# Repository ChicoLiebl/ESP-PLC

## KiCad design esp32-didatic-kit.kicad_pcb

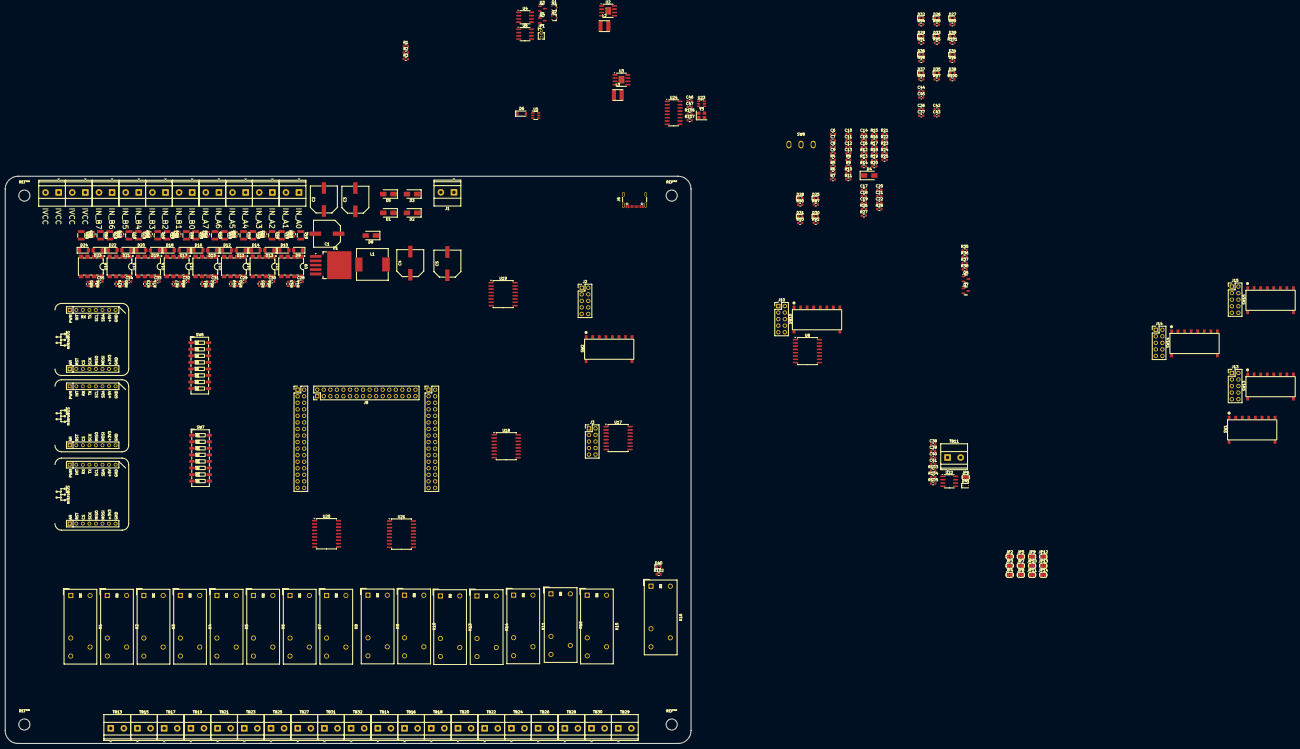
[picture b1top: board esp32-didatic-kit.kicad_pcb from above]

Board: 2 copper layers, 266.0 x 220.0 mm, 298 parts (0 on the bottom side), 241 nets, no tracks yet.

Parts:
C1, C2, C3, C4, C5: 330uF; CAP-SMD_BD10.0-L10.3-W10.3-LS10.9-FD
C6, C10, C20: 1uF; C_0603_1608Metric
C7, C8, C9, C11, C12, C13: 22uF; C_0603_1608Metric
C14, C21: 100pF; C_0603_1608Metric
C15, C16, C17, C18, C19, C28, C29, C30, C31, C32, C33, C34, C35, C36, C37, C42, C43, C44, C45: 0.1uF; C_0603_1608Metric
C22: 2.2uF; C_0603_1608Metric
C38, C40, C41: 30pF 50v; C_0603_1608Metric
C39: 100nF; C_0603_1608Metric
C46, C47: 22pF; C_0603_1608Metric
CON1, CON2, CON3: MIKROBUS_HOST_CONN
D1, D2, D3, D4, D5, D8: SS24; D_SMA
D6: PMEG3010ER,115; D_SOD-123
D9, D10, D11, D12, D13, D14, D15, D16, D17, D18, D19, D20, D21, D22, D23, D24: LL4148; D_MiniMELF
D25, D26, D27, D28, D29, D30, D31, D32, D33, D34, D35, D36, D37, D38, D39, D40: LED; LED_0603_1608Metric
D41: BAT54J; D_SOD-323F
J1: Power Input; TerminalBlock_Phoenix_MKDS-1,5-2-5.08_1x02_P5.08mm_Horizont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
J2, J3, J10, J13, J14, J15: Conn_02x05_Odd_Even; PinHeader_2x05_P2.54mm_Vertical
J6: USB_C_Receptacle; USB_C_Receptacle_GCT_USB4105-xx-A_16P_TopMnt_Horizontal
J8: MCU_MODULE_CONN; mcu_conn
JP1: REF-SEL; PinHeader_1x03_P1.27mm_Vertical
JP2, JP3, JP4, JP5, JP7, JP8, JP9, JP10, JP11, JP12, JP13, JP14: Jumper_2_Bridged; SolderJumper-2_P1.3mm_Bridged_RoundedPad1.0x1.5mm
JP6: SolderJumper_2_Open; SolderJumper-2_P1.3mm_Open_RoundedPad1.0x1.5mm
K1, K2, K3, K4, K5, K6, K7, K8, K9, K10, K11, K12, K13, K14, K15, K16: G2RL-1; Relay_SPDT_Omron_G2RL-1
L1: SMDRI127-221MT; IND-SMD_L12.3-W12.3_SMDRI127
L2, L3: 10uH; IND-SMD_L4.0-W4.0_FNR40XXS
Q1: DMP2160UW-7; SOT-323_SC-70
Q2: PDTC114EU,115; SOT-323_SC-70
Q3, Q4: DMN2058U-7; SOT-23
Q5, Q7: 2N7002; SOT-23
R1: 1.2k; R_0603_1608Metric
R2: 510; R_0603_1608Metric
R3, R4, R8, R18, R19, R21, R23, R24, R25, R26, R27, R39, R40, R45, R46, R51, R52, R57, R58, R63, R64, R69, R70, R75, R76, R81, R82: 10k; R_0603_1608Metric
R5: 4.7k; R_0603_1608Metric
R6, R14, R43, R44, R49, R50, R55, R56, R61, R62, R67, R68, R73, R74, R79, R80, R85, R86: 100k; R_0603_1608Metric
R7, R11: 20k; R_0603_1608Metric
R9, R10: 30k; R_0603_1608Metric
R12: 22K; R_0603_1608Metric
R13: 27K; R_0603_1608Metric
R15, R17: 1k; R_0603_1608Metric
R16: 3.3k; R_0603_1608Metric
R20: 470R; R_0603_1608Metric
R22: 100R; R_0603_1608Metric
R28: 10R; R_0603_1608Metric
R35, R36, R37, R38, R104, R105: 4K7; R_0603_1608Metric
R41, R42, R47, R48, R53, R54, R59, R60, R65, R66, R71, R72, R77, R78, R83, R84: 390R; R_1210_3225Metric
R87, R88, R89, R90, R91, R92, R93, R94, R95, R96, R97, R98, R99, R100, R101, R102: 18k; R_0603_1608Metric
R103: 2K; R_0603_1608Metric
R106, R107: 5K1; R_0603_1608Metric
SW1, SW2, SW10, SW13, SW14, SW15: TDS08SGRNTU04
SW6, SW7: SW_DIP_x08; SW_DIP_SPSTx08_Slide_6.7x21.88mm_W6.73mm_P2.54mm_LowProfile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
SW8: SS-12D10L5; SW-TH_SS-12D10L5
TB1, TB2, TB3, TB4, TB5, TB6, TB7, TB8, TB9, TB10, TB11, TB13, TB14, TB15, TB16, TB17, TB18, TB19, TB20, TB21, TB22, TB23, TB24, TB25, TB26, TB27, TB28, TB29, TB30, TB31, TB32: MKDSN 1,5/ 2-5,08; TerminalBlock_Phoenix_MKDS-1,5-2-5.08_1x02_P5.08mm_Horizont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
U1: LM2575-12BU; TO-263-5_TabPin3
U2, U3: ST1S10PHR; SOIC-8-1EP_3.9x4.9mm_P1.27mm_EP2.29x3mm_ThermalVias
U4: MCP6H02T-E/SN; SOIC-8_3.9x4.9mm_P1.27mm
U5: MCP4726A0T-E/CH; SOT-23-6
U6: MCP1501-40E/SN; SOIC-8_3.9x4.9mm_P1.27mm
U8, U17, U18, U19: PCF8574AT; SOIC-16W_7.5x10.3mm_P1.27mm
U9, U10, U11, U12, U13, U14, U15, U16: HCPL2630SDVM; PDIP8_GW
U20, U21: ULN2803A; SOIC-18W_7.5x11.6mm_P1.27mm
U22: SN65HVD231; SOIC-8_3.9x4.9mm_P1.27mm
U23: USBLC6-2SC6; SOT-23-6
U24: CH340G; SOIC-16_3.9x9.9mm_P1.27mm
Y3: 12MHz; Crystal_SMD_3225-4Pin_3.2x2.5mm

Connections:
+3V3: C12.1, C13.1, C36.1, C42.1, C44.1, CON1.P7 (3V3), CON2.P7 (3V3), CON3.P7 (3V3), J8.65 (3V3), JP1.3 (B), L3.2, Q5.1 (G), Q7.1 (G), R9.2, R23.2, R24.2, R25.2, R35.1, R36.1, R105.2, U24.4 (V3), U24.16 (VCC)
+5V: C8.1, C9.1, C18.1, C20.1, C28.1, C29.1, C30.1, C31.1, C32.1, C33.1, C34.1, C35.1, C37.1, C39.1, C43.1, C45.1, CON1.P10 (5V), CON2.P10 (5V), CON3.P10 (5V), J2.9, J3.9, J8.1 (5V), J10.9, J13.9, J14.9, J15.9, JP3.1 (A), JP4.1 (A), JP7.1 (A), JP9.1 (A), L2.2, R5.2, R37.1, R38.1, R43.2, R44.2, R49.2, R50.2, R55.2, R56.2, R61.2, R62.2, R67.2, R68.2, R73.2, R74.2, R79.2, R80.2, R85.2, R86.2, R104.2, SW1.10, SW2.10, SW10.10, SW13.10, SW14.10, SW15.10, TB30.1, U5.3 (VDD), U6.1 (VDD), U6.3 (~SHDN), U8.16 (VDD), U9.8 (VCC), U10.8 (VCC), U11.8 (VCC), U12.8 (VCC), U13.8 (VCC), U14.8 (VCC), U15.8 (VCC), U16.8 (VCC), U17.16 (VDD), U18.16 (VDD), U19.16 (VDD), U22.3 (VCC)
+12V: C4.1, C5.1, C6.1, C7.1, C10.1, C11.1, K1.A2, K2.A2, K3.A2, K4.A2, K5.A2, K6.A2, K7.A2, K8.A2, K9.A2, K10.A2, K11.A2, K12.A2, K13.A2, K14.A2, K15.A2, K16.A2, L1.2, R3.2, R4.2, R8.2, R87.1, R88.1, R89.1, R90.1, R91.1, R92.1, R93.1, R94.1, R95.1, R96.1, R97.1, R98.1, R99.1, R100.1, R101.1, R102.1, TB29.1, U2.1 (VIN_A), U2.6 (VIN_SW), U3.1 (VIN_A), U3.6 (VIN_SW), U4.8 (VDD), U20.10 (COM), U21.10 (COM)
/Can Bus/CAN.RX: D41.2 (A), J8.77 (CAN.RX), R105.1
/Can Bus/CAN.TX: J8.75 (CAN.TX), R103.2
/Can Bus/CAN_H: C41.1, TB11.2, U22.7 (CANH)
/Can Bus/CAN_L: C40.1, TB11.1, U22.6 (CANL)
/IO/ADDR0: JP4.2 (B), JP5.2 (B), JP9.2 (B), JP12.2 (B)
/IO/ADDR1: JP3.2 (B), JP7.2 (B), JP10.2 (B), JP13.2 (B)
/IO/ADDR2: JP2.2 (B), JP8.2 (B), JP11.2 (B), JP14.2 (B)
/IO/I2C.SCL: Q5.3 (D), R38.2, U8.14 (SCL), U17.14 (SCL), U18.14 (SCL), U19.14 (SCL)
/IO/I2C.SDA: Q7.3 (D), R37.2, U8.15 (SDA), U17.15 (SDA), U18.15 (SDA), U19.15 (SDA)
/IO/IO PortC/ADDR[0..2]: U8.1 (A0), U8.2 (A1), U8.3 (A2)
/IO/IO PortC/P0: J10.1, R44.1, SW10.1, U8.4 (P0), U9.7 (VO1)
/IO/IO PortC/P1: J10.2, R43.1, SW10.2, U8.5 (P1), U9.6 (VO2)
/IO/IO PortC/P2: J10.3, R56.1, SW10.3, U8.6 (P2), U11.7 (VO1)
/IO/IO PortC/P3: J10.4, R55.1, SW10.4, U8.7 (P3), U11.6 (VO2)
/IO/IO PortC/P4: J10.5, R50.1, SW10.5, U8.9 (P4), U10.7 (VO1)
/IO/IO PortC/P5: J10.6, R49.1, SW10.6, U8.10 (P5), U10.6 (VO2)
/IO/IO PortC/P6: J10.7, R62.1, SW10.7, U8.11 (P6), U12.7 (VO1)
/IO/IO PortC/P7: J10.8, R61.1, SW10.8, U8.12 (P7), U12.6 (VO2)
/IO/IO PortD/ADDR[0..2]: U17.1 (A0), U17.2 (A1), U17.3 (A2)
/IO/IO PortD/P0: J13.1, R68.1, SW13.1, U13.7 (VO1), U17.4 (P0)
/IO/IO PortD/P1: J13.2, R67.1, SW13.2, U13.6 (VO2), U17.5 (P1)
/IO/IO PortD/P2: J13.3, R74.1, SW13.3, U14.7 (VO1), U17.6 (P2)
/IO/IO PortD/P3: J13.4, R73.1, SW13.4, U14.6 (VO2), U17.7 (P3)
/IO/IO PortD/P4: J13.5, R80.1, SW13.5, U15.7 (VO1), U17.9 (P4)
/IO/IO PortD/P5: J13.6, R79.1, SW13.6, U15.6 (VO2), U17.10 (P5)
/IO/IO PortD/P6: J13.7, R86.1, SW13.7, U16.7 (VO1), U17.11 (P6)
/IO/IO PortD/P7: J13.8, R85.1, SW13.8, U16.6 (VO2), U17.12 (P7)
/IO/IO PortE/ADDR[0..2]: U18.1 (A0), U18.2 (A1), U18.3 (A2)
/IO/IO PortE/P0: J14.1, SW6.1, SW14.1, U18.4 (P0)
/IO/IO PortE/P1: J14.2, SW6.2, SW14.2, U18.5 (P1)
/IO/IO PortE/P2: J14.3, SW6.3, SW14.3, U18.6 (P2)
/IO/IO PortE/P3: J14.4, SW6.4, SW14.4, U18.7 (P3)
/IO/IO PortE/P4: J14.5, SW6.5, SW14.5, U18.9 (P4)
/IO/IO PortE/P5: J14.6, SW6.6, SW14.6, U18.10 (P5)
/IO/IO PortE/P6: J14.7, SW6.7, SW14.7, U18.11 (P6)
/IO/IO PortE/P7: J14.8, SW6.8, SW14.8, U18.12 (P7)
/IO/IO PortF/ADDR[0..2]: U19.1 (A0), U19.2 (A1), U19.3 (A2)
/IO/IO PortF/P0: J15.1, SW7.1, SW15.1, U19.4 (P0)
/IO/IO PortF/P1: J15.2, SW7.2, SW15.2, U19.5 (P1)
/IO/IO PortF/P2: J15.3, SW7.3, SW15.3, U19.6 (P2)
/IO/IO PortF/P3: J15.4, SW7.4, SW15.4, U19.7 (P3)
/IO/IO PortF/P4: J15.5, SW7.5, SW15.5, U19.9 (P4)
/IO/IO PortF/P5: J15.6, SW7.6, SW15.6, U19.10 (P5)
/IO/IO PortF/P6: J15.7, SW7.7, SW15.7, U19.11 (P6)
/IO/IO PortF/P7: J15.8, SW7.8, SW15.8, U19.12 (P7)
/IO/Inputs/Isolated Input/IVCC: R39.2, R40.1, R41.1, R42.1, R45.2, R46.1, R47.1, R48.1, R51.2, R52.1, R53.1, R54.1, R57.2, R58.1, R59.1, R60.1, R63.2, R64.1, R65.1, R66.1, R69.2, R70.1, R71.1, R72.1, R75.2, R76.1, R77.1, R78.1, R81.2, R82.1, R83.1, R84.1, TB9.1, TB9.2, TB10.1, TB10.2
/IO/Inputs/RAW_A0: D9.2 (A), R39.1, TB1.1, U9.2 (VF1-)
/IO/Inputs/RAW_A1: D10.2 (A), R40.2, TB1.2, U9.3 (VF2-)
/IO/Inputs/RAW_A2: D13.2 (A), R51.1, TB2.1, U11.2 (VF1-)
/IO/Inputs/RAW_A3: D14.2 (A), R52.2, TB2.2, U11.3 (VF2-)
/IO/Inputs/RAW_A4: D11.2 (A), R45.1, TB3.1, U10.2 (VF1-)
/IO/Inputs/RAW_A5: D12.2 (A), R46.2, TB3.2, U10.3 (VF2-)
/IO/Inputs/RAW_A6: D15.2 (A), R57.1, TB4.1, U12.2 (VF1-)
/IO/Inputs/RAW_A7: D16.2 (A), R58.2, TB4.2, U12.3 (VF2-)
/IO/Inputs/RAW_B0: D17.2 (A), R63.1, TB5.1, U13.2 (VF1-)
/IO/Inputs/RAW_B1: D18.2 (A), R64.2, TB5.2, U13.3 (VF2-)
/IO/Inputs/RAW_B2: D19.2 (A), R69.1, TB6.1, U14.2 (VF1-)
/IO/Inputs/RAW_B3: D20.2 (A), R70.2, TB6.2, U14.3 (VF2-)
/IO/Inputs/RAW_B4: D21.2 (A), R75.1, TB7.1, U15.2 (VF1-)
/IO/Inputs/RAW_B5: D22.2 (A), R76.2, TB7.2, U15.3 (VF2-)
/IO/Inputs/RAW_B6: D23.2 (A), R81.1, TB8.1, U16.2 (VF1-)
/IO/Inputs/RAW_B7: D24.2 (A), R82.2, TB8.2, U16.3 (VF2-)
/IO/OutputE/COMM0: K1.11, K3.11, TB31.2
/IO/OutputE/COMM1: K4.11, K5.11, K6.11, K8.11, TB31.1
/IO/OutputE/NC0: K1.12, TB13.2
/IO/OutputE/NC1: K2.12, TB15.2
/IO/OutputE/NC2: K3.12, TB17.2
/IO/OutputE/NC3: K4.12, TB19.2
/IO/OutputE/NC4: K5.12, TB21.2
/IO/OutputE/NC5: K6.12, TB23.2
/IO/OutputE/NC6: K7.12, TB25.2
/IO/OutputE/NC7: K8.12, TB27.2
/IO/OutputE/NO0: K1.14, TB13.1
/IO/OutputE/NO1: K2.14, TB15.1
/IO/OutputE/NO2: K3.14, TB17.1
/IO/OutputE/NO3: K4.14, K5.14, TB19.1, TB21.1
/IO/OutputE/NO5: K6.14, TB23.1
/IO/OutputE/NO6: K7.14, TB25.1
/IO/OutputE/NO7: K8.14, TB27.1
/IO/OutputE/OUT0: SW6.16, U20.1 (I1)
/IO/OutputE/OUT1: SW6.15, U20.2 (I2)
/IO/OutputE/OUT2: SW6.14, U20.3 (I3)
/IO/OutputE/OUT3: SW6.13, U20.4 (I4)
/IO/OutputE/OUT4: SW6.12, U20.5 (I5)
/IO/OutputE/OUT5: SW6.11, U20.6 (I6)
/IO/OutputE/OUT6: SW6.10, U20.7 (I7)
/IO/OutputE/OUT7: SW6.9, U20.8 (I8)
/IO/OutputE/REL0: D25.1 (K), K1.A1, U20.18 (O1)
/IO/OutputE/REL2: D27.1 (K), K3.A1, U20.16 (O3)
/IO/OutputE/REL3: D28.1 (K), K4.A1, U20.15 (O4)
/IO/OutputE/REL4: D29.1 (K), K5.A1, U20.14 (O5)
/IO/OutputE/REL5: D30.1 (K), K6.A1, U20.13 (O6)
/IO/OutputE/REL6: D31.1 (K), K7.A1, U20.12 (O7)
/IO/OutputE/REL7: D32.1 (K), K8.A1, U20.11 (O8)
/IO/OutputE/Relay Circuit1/Coil: D26.1 (K), K2.A1
/IO/OutputF/COMM0: K9.11, K13.11, TB32.2
/IO/OutputF/COMM1: K11.11, K12.11, K14.11, K16.11, TB32.1
/IO/OutputF/NC0: K9.12, TB14.2
/IO/OutputF/NC1: K10.12, TB16.2
/IO/OutputF/NC2: K13.12, TB18.2
/IO/OutputF/NC3: K14.12, TB20.2
/IO/OutputF/NC4: K11.12, TB22.2
/IO/OutputF/NC5: K12.12, TB24.2
/IO/OutputF/NC6: K15.12, TB26.2
/IO/OutputF/NC7: K16.12, TB28.2
/IO/OutputF/NO0: K9.14, TB14.1
/IO/OutputF/NO1: K10.14, TB16.1
/IO/OutputF/NO2: K13.14, TB18.1
/IO/OutputF/NO3: K11.14, K14.14, TB20.1, TB22.1
/IO/OutputF/NO5: K12.14, TB24.1
/IO/OutputF/NO6: K15.14, TB26.1
/IO/OutputF/NO7: K16.14, TB28.1
/IO/OutputF/OUT0: SW7.16, U21.1 (I1)
/IO/OutputF/OUT1: SW7.15, U21.2 (I2)
/IO/OutputF/OUT2: SW7.14, U21.3 (I3)
/IO/OutputF/OUT3: SW7.13, U21.4 (I4)
/IO/OutputF/OUT4: SW7.12, U21.5 (I5)
/IO/OutputF/OUT5: SW7.11, U21.6 (I6)
/IO/OutputF/OUT6: SW7.10, U21.7 (I7)
/IO/OutputF/OUT7: SW7.9, U21.8 (I8)
/IO/OutputF/REL0: D33.1 (K), K9.A1, U21.18 (O1)
/IO/OutputF/REL2: D37.1 (K), K13.A1, U21.16 (O3)
/IO/OutputF/REL3: D38.1 (K), K14.A1, U21.15 (O4)
/IO/OutputF/REL4: D35.1 (K), K11.A1, U21.14 (O5)
/IO/OutputF/REL5: D36.1 (K), K12.A1, U21.13 (O6)
/IO/OutputF/REL6: D39.1 (K), K15.A1, U21.12 (O7)
/IO/OutputF/REL7: D40.1 (K), K16.A1, U21.11 (O8)
/IO/OutputF/Relay Circuit1/Coil: D34.1 (K), K10.A1
/IO/PA0: J2.1, J8.33 (PA.0), SW1.1
/IO/PA1: J2.2, J8.35 (PA.1), SW1.2
/IO/PA2: J2.3, J8.37 (PA.2), SW1.3
/IO/PA3: J2.4, J8.39 (PA.3), SW1.4
/IO/PA4: J2.5, J8.41 (PA.4), SW1.5
/IO/PA5: J2.6, J8.43 (PA.5), SW1.6
/IO/PA6: J2.7, J8.45 (PA.6), SW1.7
/IO/PA7: J2.8, J8.47 (PA.7), SW1.8
/IO/PB0: J3.1, J8.49 (PB.0), SW2.1
/IO/PB1: J3.2, J8.51 (PB.1), SW2.2
/IO/PB2: J3.3, J8.53 (PB.2), SW2.3
/IO/PB3: J3.4, J8.55 (PB.3), SW2.4
/IO/PB4: J3.5, J8.57 (PB.4), SW2.5
/IO/PB5: J3.6, J8.59 (PB.5), SW2.6
/IO/PB6: J3.7, J8.61 (PB.6), SW2.7
/IO/PB7: J3.8, J8.63 (PB.7), SW2.8
/MCU/HSPI.CS: CON3.P3 (CS), J8.17 (SPI1.CS)
/MCU/HSPI.MISO: CON3.P5 (MISO), J8.13 (SPI1.MISO)
/MCU/HSPI.MOSI: CON3.P6 (MOSI), J8.15 (SPI1.MOSI)
/MCU/HSPI.SCK: CON3.P4 (SCK), J8.11 (SPI1.SCK)
/MCU/I2C0.SCL: J8.67 (I2C0.SCL), Q5.2 (S), R36.2
/MCU/I2C0.SDA: Q7.2 (S), R35.2
/MCU/I2C1.SCL: CON1.P12 (SCL), CON2.P12 (SCL), CON3.P12 (SCL), J8.71 (I2C1.SCL)
/MCU/I2C1.SDA: CON1.P11 (SDA), CON2.P11 (SDA), CON3.P11 (SDA), J8.73 (I2C1.SDA)
/MCU/VSPI.MISO: CON1.P5 (MISO), CON2.P5 (MISO), J8.81 (SPI0.MISO)
/MCU/VSPI.MOSI: CON1.P6 (MOSI), CON2.P6 (MOSI), J8.83 (SPI0.MOSI)
/MCU/VSPI.SCK: CON1.P4 (SCK), CON2.P4 (SCK), J8.79 (SPI0.SCK)
/Power Supply/Programable Voltage Reference/VREF: JP1.1 (A), R26.2, U5.1 (VOUT)
/Power Supply/Programable Voltage Reference/VREF_4.096V: C17.1, C22.1, R28.2, U5.6 (VREF)
/Power Supply/VPP_CONN_RST: Q4.1 (G), R25.1
/Power Supply/VPP_DAC: R12.2, U4.3 (INA+)
/Power Supply/VPP_en: Q2.1 (B), R21.2
/Power Supply/VPP_sense: C16.1, R16.2, R17.1
/Power Supply/VREF_DAC_Sense: C19.1, R26.1, R27.2
/Power Supply/Vraw: C1.1, C2.1, C3.1, D2.1 (K), D3.1 (K), U1.1 (VIN)
/USB-SERIAL/DBG_UART.DTR: J8.7 (UART0.IO0), U24.13 (~DTR)
/USB-SERIAL/DBG_UART.RTS: J8.9 (UART0.EN), U24.14 (~RTS)
/USB-SERIAL/DBG_UART.RX: J8.3 (UART0.TX), U24.3 (RXD)
/USB-SERIAL/DBG_UART.TX: J8.5 (UART0.RX), U24.2 (TXD)
GND: C1.2, C2.2, C3.2, C4.2, C5.2, C6.2, C7.2, C8.2, C9.2, C10.2, C11.2, C12.2, C13.2, C15.2, C16.2, C17.2, C18.2, C19.2, C20.2, C21.2, C22.2, C28.2, C29.2, C30.2, C31.2, C32.2, C33.2, C34.2, C35.2, C36.2, C37.2, C38.2, C39.2, C40.2, C41.2, C42.2, C43.2, C44.2, C45.2, C46.2, C47.2, CON1.P8 (GND1), CON1.P9 (GND2), CON2.P8 (GND1), CON2.P9 (GND2), CON3.P8 (GND1), CON3.P9 (GND2), D1.2 (A), D5.2 (A), D8.2 (A), J2.10, J3.10, J6.A1 (GND), J6.A12 (GND), J6.B1 (GND), J6.B12 (GND), J6.S1 (SHIELD), J8.2 (GND), J8.4 (GND), J8.6 (GND), J8.8 (GND), J8.10 (GND), J8.12 (GND), J8.14 (GND), J8.16 (GND), J8.18 (GND), J8.20 (GND), J8.22 (GND), J8.24 (GND), J8.26 (GND), J8.28 (GND), J8.30 (GND), J8.32 (GND), J8.34 (GND), J8.36 (GND), J8.38 (GND), J8.40 (GND), J8.42 (GND), J8.44 (GND), J8.46 (GND), J8.48 (GND), J8.50 (GND), J8.52 (GND), J8.54 (GND), J8.56 (GND), J8.58 (GND), J8.60 (GND), J8.62 (GND), J8.64 (GND), J8.66 (GND), J8.70 (GND), J8.72 (GND), J8.74 (GND), J8.76 (GND), J8.78 (GND), J8.80 (GND), J8.82 (GND), J8.84 (GND), J8.86 (GND), J8.88 (GND), J8.90 (GND), J8.92 (GND), J8.94 (GND), J8.96 (GND), J10.10, J13.10, J14.10, J15.10, JP2.1 (A), JP5.1 (A), JP6.2 (B), JP8.1 (A), JP10.1 (A), JP11.1 (A), JP12.1 (A), JP13.1 (A), JP14.1 (A), Q2.2 (E), Q3.2 (S), Q4.2 (S), R1.1, R7.1, R11.1, R12.1, R13.1, R17.2, R21.1, R27.1, R106.1, R107.2, SW1.9, SW2.9, SW10.9, SW13.9, SW14.9, SW15.9, TB29.2, TB30.2, U1.3 (GND), U2.4 (AGND), U2.5 (SYNC), U2.8 (PGND), U2.9 (EPAD), U3.4 (AGND), U3.5 (SYNC), U3.8 (PGND), U3.9 (EPAD), U4.4 (VSS), U5.2 (VSS), U6.2 (GND), U6.4 (GND), U6.5 (GND), U6.6 (GND), U8.8 (GND), U9.5 (GND), U10.5 (GND), U11.5 (GND), U12.5 (GND), U13.5 (GND), U14.5 (GND), U15.5 (GND), U16.5 (GND), U17.8 (GND), U18.8 (GND), U19.8 (GND), U20.9 (GND), U21.9 (GND), U22.2 (GND), U23.2 (GND), U24.1 (GND)
unnamed: D1.1 (K), D2.2 (A), J1.2
unnamed: D3.2 (A), D5.1 (K), SW8.3
unnamed: D4.2 (A), R23.1
unnamed: D4.1 (K), Q3.3 (D), R22.2
unnamed: D6.2, R20.2
unnamed: D8.1 (K), L1.1, U1.2 (OUT)
unnamed: D9.1 (K), R41.2, U9.1 (VF1+)
unnamed: D10.1 (K), R42.2, U9.4 (VF2+)
unnamed: D11.1 (K), R47.2, U10.1 (VF1+)
unnamed: D12.1 (K), R48.2, U10.4 (VF2+)
unnamed: D13.1 (K), R53.2, U11.1 (VF1+)
unnamed: D14.1 (K), R54.2, U11.4 (VF2+)
unnamed: D15.1 (K), R59.2, U12.1 (VF1+)
unnamed: D16.1 (K), R60.2, U12.4 (VF2+)
unnamed: D17.1 (K), R65.2, U13.1 (VF1+)
unnamed: D18.1 (K), R66.2, U13.4 (VF2+)
unnamed: D19.1 (K), R71.2, U14.1 (VF1+)
unnamed: D20.1 (K), R72.2, U14.4 (VF2+)
unnamed: D21.1 (K), R77.2, U15.1 (VF1+)
unnamed: D22.1 (K), R78.2, U15.4 (VF2+)
unnamed: D23.1 (K), R83.2, U16.1 (VF1+)
unnamed: D24.1 (K), R84.2, U16.4 (VF2+)
unnamed: D25.2 (A), R87.2
unnamed: D26.2 (A), R88.2
unnamed: D27.2 (A), R89.2
unnamed: D28.2 (A), R90.2
unnamed: D29.2 (A), R91.2
unnamed: D30.2 (A), R92.2
unnamed: D31.2 (A), R93.2
unnamed: D32.2 (A), R94.2
unnamed: D33.2 (A), R95.2
unnamed: D34.2 (A), R96.2
unnamed: D35.2 (A), R97.2
unnamed: D36.2 (A), R98.2
unnamed: D37.2 (A), R99.2
unnamed: D38.2 (A), R100.2
unnamed: D39.2 (A), R101.2
unnamed: D40.2 (A), R102.2
unnamed: D41.1 (K), U22.4 (R)
unnamed: J1.1, SW8.2
unnamed: J6.A5 (CC1), R106.2
unnamed: J6.B5 (CC2), R107.1
unnamed: J6.A4 (VBUS), J6.A9 (VBUS), J6.B4 (VBUS), J6.B9 (VBUS)
unnamed: JP6.1 (A), R104.1, U22.8 (Rs)
unnamed: Q1.3 (D), R20.1
unnamed: Q1.1 (G), R18.1, R19.2
unnamed: Q1.2 (S), R16.1, R18.2, U4.6 (INB-), U4.7 (OUTB)
unnamed: Q2.3 (C), R19.1
unnamed: Q3.1 (G), Q4.3 (D), R24.1
unnamed: R2.2, R3.1
unnamed: R5.1, R6.2
unnamed: R9.1, R10.2
unnamed: R1.2, R2.1, U1.4 (FB)
unnamed: R4.1, U2.2 (INH(EN))
unnamed: L2.1, U2.7 (SW)
unnamed: R6.1, R7.2, U2.3 (VFB)
unnamed: R8.1, U3.2 (INH(EN))
unnamed: L3.1, U3.7 (SW)
unnamed: R10.1, R11.2, U3.3 (VFB)
unnamed: C14.2, R13.2, R14.1, U4.2 (INA-)
unnamed: C14.1, R14.2, R15.2, U4.1 (OUTA)
unnamed: C15.1, R15.1, U4.5 (INB+)
unnamed: C21.1, R28.1, U6.7 (OUT), U6.8 (FEEDBACK)
unnamed: R103.1, U22.1 (D)
unnamed: C38.1, U22.5 (Vref)
unnamed: J6.A6 (D+), J6.B6 (D+), U23.1 (I/O1), U24.5 (UD+)
unnamed: J6.A7 (D-), J6.B7 (D-), U23.6 (I/O1), U24.6 (UD-)
unnamed: C47.1, U24.7 (XI), Y3.1
unnamed: C46.1, U24.8 (XO), Y3.3
VPP: D6.1, R22.1

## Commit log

2025-09-16 Use kicad footprints
2025-09-17 add MCU + output
2025-09-21 add mcu module + position components
2025-09-21 fix models
2025-09-21 Updated MCU to MCU module + set SMD comp. footprints
2025-09-26 add PA an PB ports
2025-10-01 updated silk + started routing
2025-10-06 routed buses
2025-10-29 finished routing SPI, I2C and MikroBUS
